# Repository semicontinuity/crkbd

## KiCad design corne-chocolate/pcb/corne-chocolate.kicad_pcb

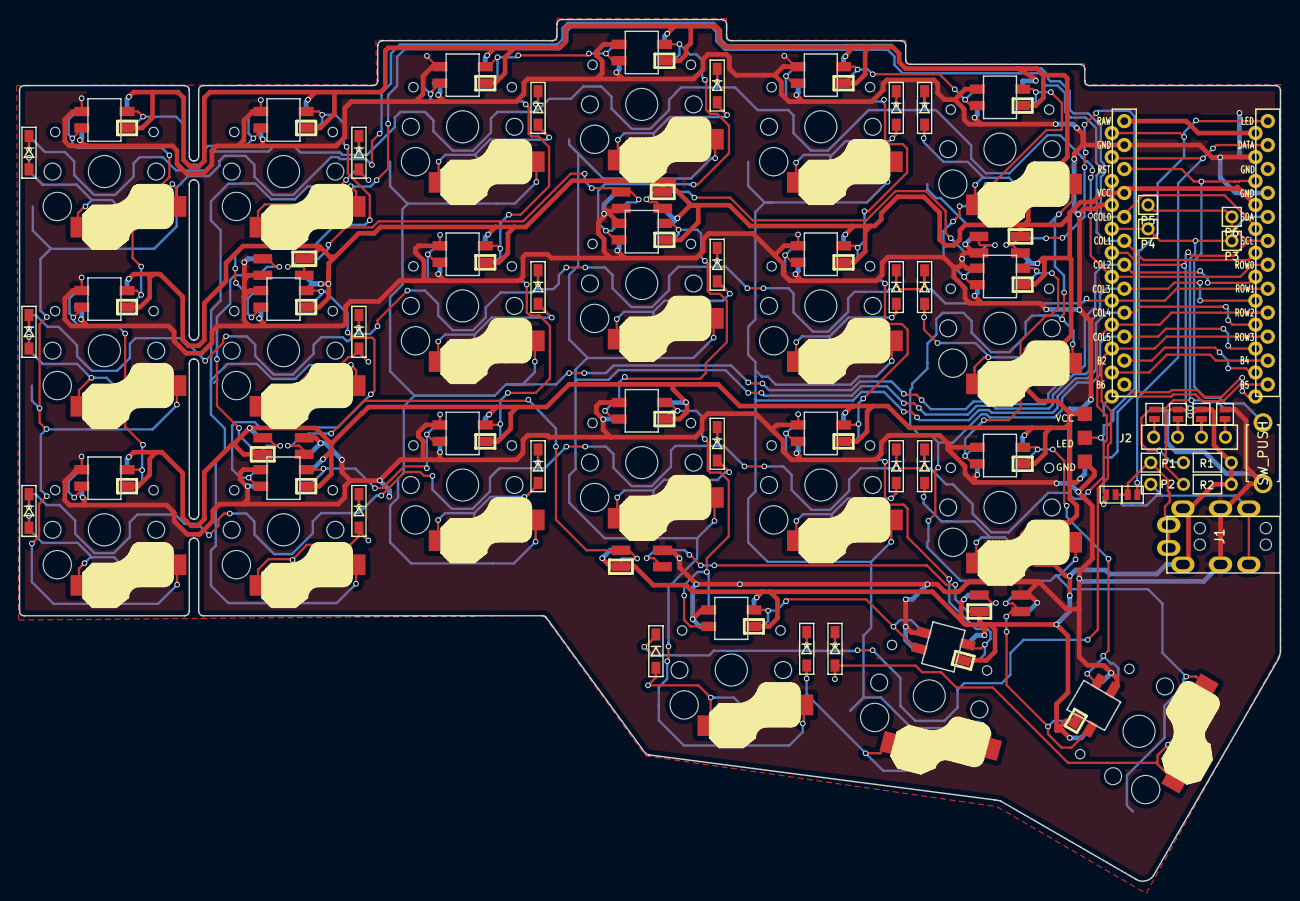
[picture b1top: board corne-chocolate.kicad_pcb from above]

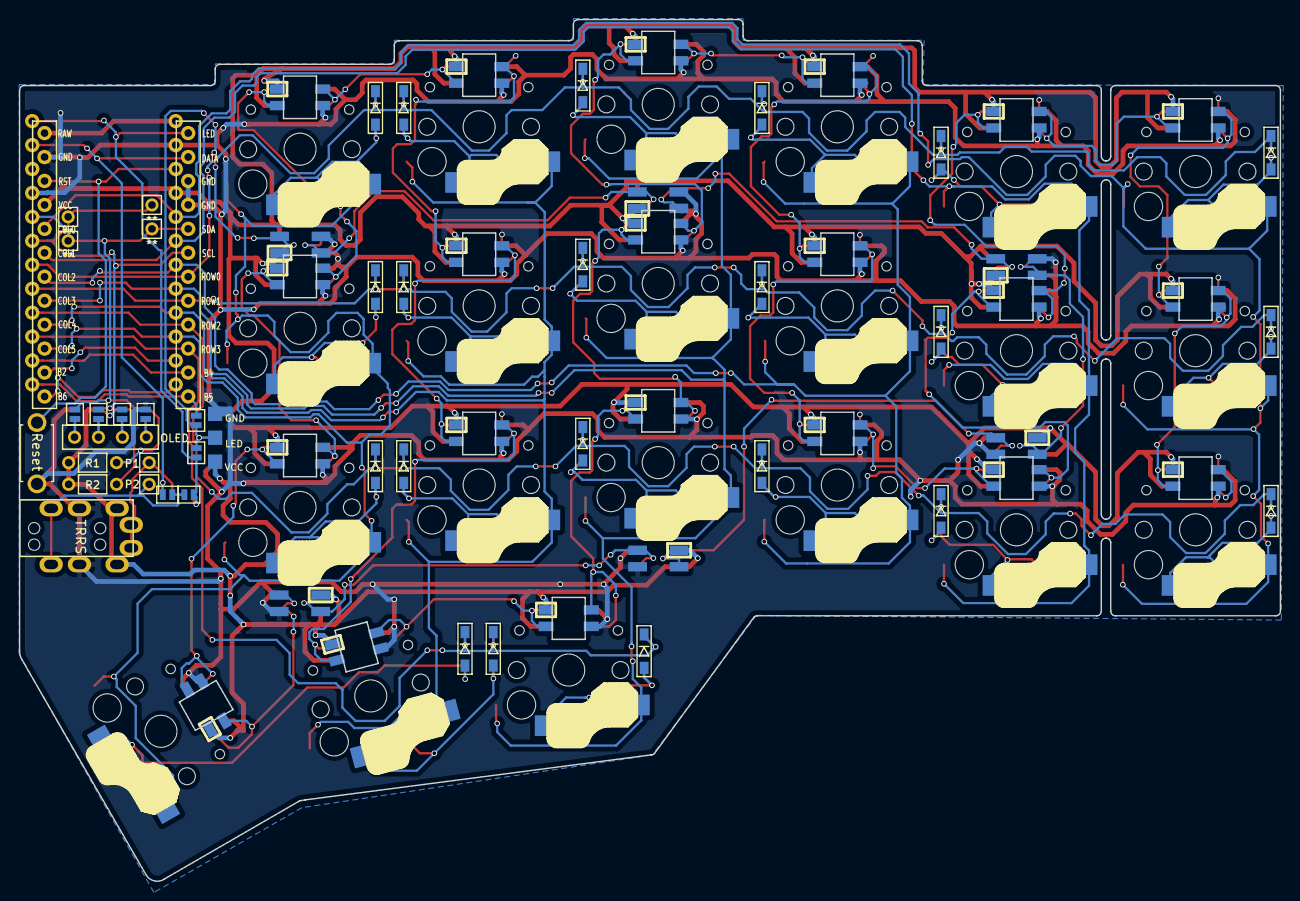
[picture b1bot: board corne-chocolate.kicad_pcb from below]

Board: 2 copper layers, 133.8 x 91.4 mm, 96 parts (8 on the bottom side), 72 nets.

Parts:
D1, D2, D3, D4, D5, D6, D7, D8, D9, D10, D11, D12, D13, D14, D15, D16, D17, D18, D19, D20, D21: D; D3_SMD
J1: MJ-4PP-9
J2: OLED
J3: LED; StripLED_rev
JP1, JP2, JP3, JP4, JP5, JP6, JP7, JP8, JP9, JP10, JP11, JP12, JP13, JP14: Jumper
L1, L2, L3, L4, L5, L6, L7, L8, L9, L10, L11, L12, L13, L14, L15, L16, L17, L18, L19, L20, L21: SK6812MINI; SK6812MINI_rev
L22, L23, L24, L25, L26, L27: SK6812MINI; SK6812MINI_underglow_rev
P1, P2, P3, P4, P5, P6: i2c-pin; 1pin_conn
R1, R2: R
RSW1: SW_PUSH; ResetSW
SW1, SW2, SW3, SW4, SW5, SW6, SW7, SW8, SW9, SW10, SW11, SW12, SW13, SW14, SW15, SW16, SW17, SW18, SW19, SW20: SW_PUSH; Choc_Hotswap
SW21: SW_PUSH; Choc_Hotswap_1.5u
U1: ProMicro; ProMicro_v2

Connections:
/A: J1.A, JP1.2, JP10.2, P1.1
/B: J1.B, JP11.2, JP12.2, P2.1
/BL: JP13.2, U1.12
/RX: JP10.1, JP12.1, U1.2
/TX: JP1.1, JP11.1, JP14.2, U1.1
GND: J1.C, J3.1, JP2.1, JP9.1, L1.2, L2.2, L3.2, L4.2, L5.2, L6.2, L7.2, L8.2, L9.2, L10.2, L11.2, L12.2, L13.2, L14.2, L15.2, L16.2, L17.2, L18.2, L19.2, L20.2, L21.2, L22.2, L23.2, L24.2, L25.2, L26.2, L27.2, RSW1.2, U1.4, U1.23
LED: J3.2, JP13.1, JP14.1, L24.3
unnamed: D1.2, SW1.2
unnamed: D2.2, SW2.2
unnamed: D3.2, SW3.2
unnamed: D4.2, SW4.2
unnamed: D5.2, SW5.2
unnamed: D6.2, SW6.2
unnamed: D7.2, SW7.2
unnamed: D8.2, SW8.2
unnamed: D9.2, SW9.2
unnamed: D10.2, SW10.2
unnamed: D11.2, SW11.2
unnamed: D12.2, SW12.2
unnamed: D13.2, SW13.2
unnamed: D14.2, SW14.2
unnamed: D15.2, SW15.2
unnamed: D16.2, SW16.2
unnamed: D17.2, SW17.2
unnamed: D18.2, SW18.2
unnamed: D19.2, SW19.2
unnamed: D20.2, SW20.2
unnamed: D21.2, SW21.2
unnamed: J2.1, JP5.2, JP9.2
unnamed: J2.2, JP4.2, JP8.2
unnamed: J2.3, JP3.2, JP7.2
unnamed: J2.4, JP2.2, JP6.2
unnamed: L1.1, L7.3
unnamed: L1.3, L2.1
unnamed: L2.3, L8.1
unnamed: L3.1, L9.3
unnamed: L3.3, L4.1
unnamed: L5.3, L6.1
unnamed: L4.3, L10.1
unnamed: L10.3, L16.1
unnamed: L11.1, L17.3
unnamed: L5.1, L11.3
unnamed: L6.3, L12.1
unnamed: L12.3, L18.1
unnamed: L7.1, L13.3
unnamed: L8.3, L14.1
unnamed: L14.3, L15.1
unnamed: L9.1, L15.3
unnamed: L16.3, L19.1
unnamed: L17.1, L20.3
unnamed: L18.3, L21.1
unnamed: L19.3, L20.1
unnamed: L21.3, L27.1
unnamed: L22.1, L25.3
unnamed: L22.3, L23.1
unnamed: L23.3, L24.1
unnamed: L25.1, L26.3
unnamed: L26.1, L27.3
SCL: JP4.1, JP7.1, P5.1, P6.1, R2.2, U1.6
SDA: JP5.1, JP6.1, P3.1, P4.1, R1.2, U1.5
VCC: J1.D, J3.3, JP3.1, JP8.1, L1.4, L2.4, L3.4, L4.4, L5.4, L6.4, L7.4, L8.4, L9.4, L10.4, L11.4, L12.4, L13.4, L14.4, L15.4, L16.4, L17.4, L18.4, L19.4, L20.4, L21.4, L22.4, L23.4, L24.4, L25.4, L26.4, L27.4, R1.1, R2.1, U1.21
col0: SW1.1, SW7.1, SW13.1, U1.20
col1: SW2.1, SW8.1, SW14.1, U1.19
col2: SW3.1, SW9.1, SW15.1, U1.18
col3: SW4.1, SW10.1, SW16.1, SW19.1, U1.17
col4: SW5.1, SW11.1, SW17.1, SW20.1, U1.16
col5: SW6.1, SW12.1, SW18.1, SW21.1, U1.15
reset: RSW1.1, U1.22
row0: D1.1, D2.1, D3.1, D4.1, D5.1, D6.1, U1.7
row1: D7.1, D8.1, D9.1, D10.1, D11.1, D12.1, U1.8
row2: D13.1, D14.1, D15.1, D16.1, D17.1, D18.1, U1.9
row3: D19.1, D20.1, D21.1, U1.10

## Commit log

2021-08-12 corne-chocolate: moved I2C jumpers
2021-08-12 moving tracks
2021-08-13 changed board settings
